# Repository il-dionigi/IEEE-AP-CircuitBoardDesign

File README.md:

# Schematic and Board Design
*05 February 2018 (Schematic)*

*16 February 2018 (PCB)*

This repo contains both the schematic and board files for our PCB made using EAGLE.  

Creating the schematic and board involved the culmination of all previous labs, as each of the components and wiring setups were tested or designed by our group.

The specs for both parts can be found in [schematic-spec.pdf](https://github.com/il-dionigi/Circuit-Board-Design/blob/master/schematic-spec.pdf) and [board-spec.pdf](https://github.com/il-dionigi/Circuit-Board-Design/blob/master/schematic-spec.pdf) respectively. Screenshots of the schematic may be found [here](https://github.com/il-dionigi/Circuit-Board-Design/blob/master/SchematicPictures) while screenshots of the pcb may be found [here](https://github.com/il-dionigi/Circuit-Board-Design/blob/master/BoardPictures).

**Collaborators:**  
[Brian Raymond](https://github.com/il-dionigi) | [Kevin Ke-En Sun](https://github.com/inherentlyMalicious) | [Koji Kusumi](https://github.com/kojiboji) | [Rob Griffith](https://github.com/rwgriffithv)

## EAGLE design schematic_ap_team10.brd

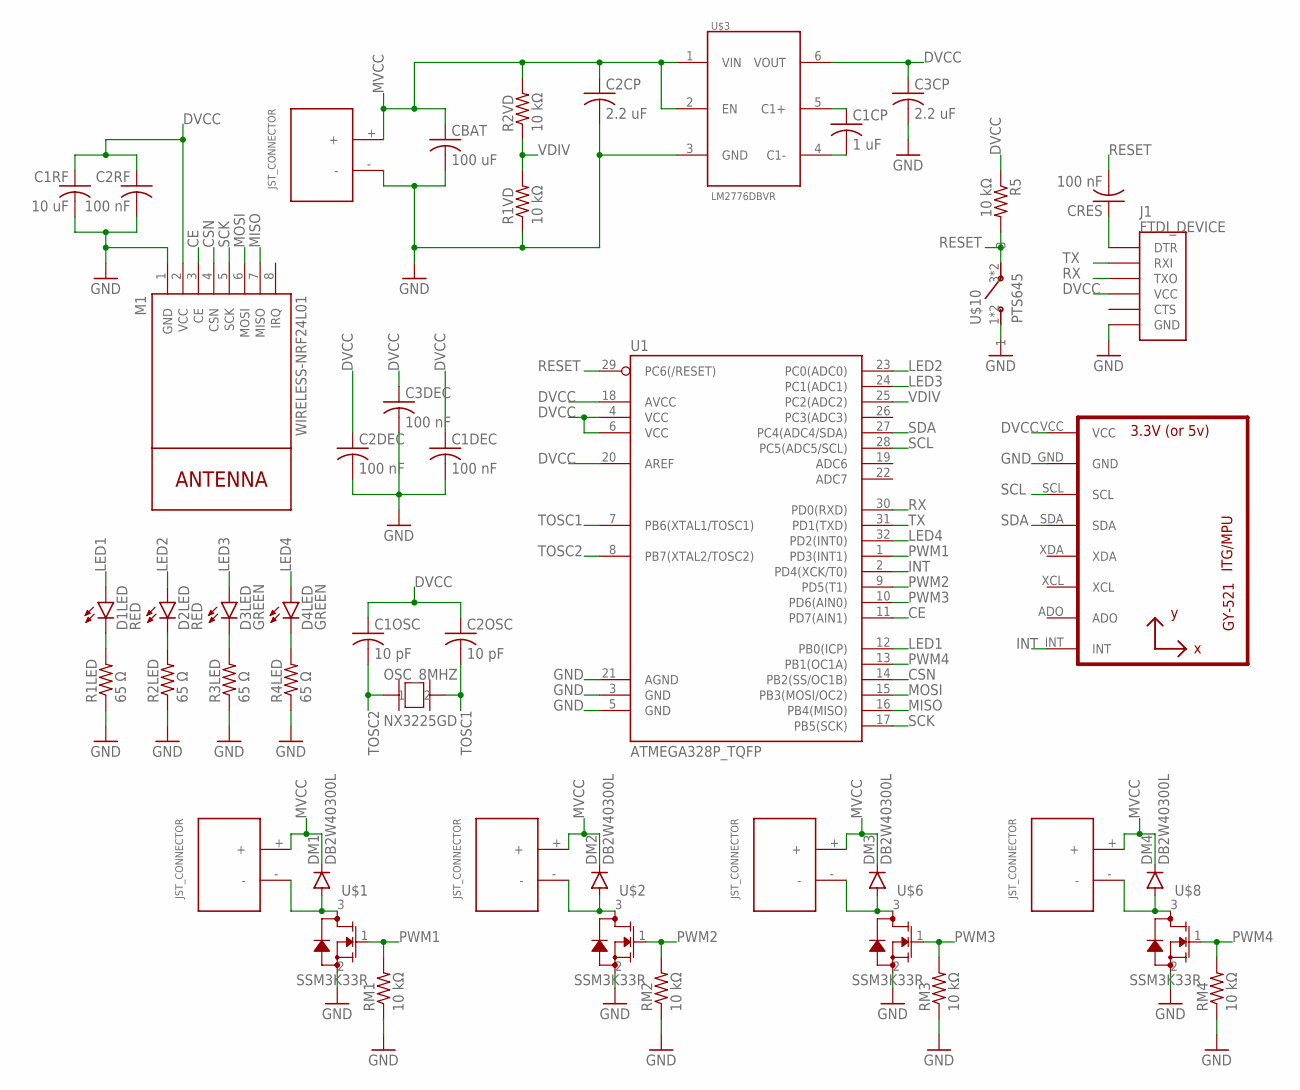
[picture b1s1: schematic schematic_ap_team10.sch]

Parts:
C1CP: 1 uF; C0603
C1DEC, C2DEC, C2RF, C3DEC: 100 nF; C0603
C1OSC, C2OSC: 10 pF; C0603
C1RF: 10 uF; C0603
C2CP, C3CP: 2.2 uF; C0603
CBAT: 100 uF; C0805
CRES: 100 nF; C0603
D1LED, D2LED: RED; LED-0603
D3LED, D4LED: GREEN; LED-0603
DM1, DM2, DM3, DM4: DB2W40300L; MINI2-F3-B
J1: FTDI_DEVICE; FTDI_DEVICE_SIDE
M1: WIRELESS-NRF24L01
OSC_8MHZ: NX3225GD; 2-SMD
R1LED, R2LED, R3LED, R4LED: 65 Ω; R0603
R1VD, R2VD, R5: 10 kΩ; R0603
RM1, RM2, RM3, RM4: 10 kΩ; R0603
U1: ATMEGA328P_TQFP; TQFP32-08
U2: GY-521MPU6050; GY-521
U$1, U$2, U$6, U$8: SSM3K33R; SOT-23F
U$3: LM2776DBVR; SOT23-5
U$4, U$5, U$7, U$9, U$11: JST_CONNECTOR_FEMALE
U$10: PTS645; SOT-35

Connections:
CE: M1.3 (CE), U1.11 (PD7(AIN1))
CSN: M1.4 (CSN), U1.14 (PB2(SS/OC1B))
DVCC: C1DEC.1, C1OSC.1, C1RF.1, C2DEC.1, C2OSC.1, C2RF.1, C3CP.1, C3DEC.1, J1.P$4 (VCC), M1.2 (VCC), R5.1, U1.4 (VCC), U1.6 (VCC), U1.18 (AVCC), U1.20 (AREF), U2.VCC, U$3.6 (VOUT)
GND: C1DEC.2, C1RF.2, C2CP.2, C2DEC.2, C2RF.2, C3CP.2, C3DEC.2, CBAT.2, J1.P$6 (GND), M1.1 (GND), R1LED.1, R1VD.1, R2LED.1, R3LED.1, R4LED.1, RM1.1, RM2.1, RM3.1, RM4.1, U1.3 (GND), U1.5 (GND), U1.21 (AGND), U2.GND, U$1.2, U$2.2, U$3.3 (GND), U$6.2, U$8.2, U$10.1, U$10.2 (1), U$11.-
INT: U1.2 (PD4(XCK/T0)), U2.INT
LED1: D1LED.A, U1.12 (PB0(ICP))
LED2: D2LED.A, U1.23 (PC0(ADC0))
LED3: D3LED.A, U1.24 (PC1(ADC1))
LED4: D4LED.A, U1.32 (PD2(INT0))
MISO: M1.7 (MISO), U1.16 (PB4(MISO))
MOSI: M1.6 (MOSI), U1.15 (PB3(MOSI/OC2))
MVCC: C2CP.1, CBAT.1, DM1.NEG (GPIN), DM2.NEG (GPIN), DM3.NEG (GPIN), DM4.NEG (GPIN), R2VD.2, U$3.1 (VIN), U$3.2 (EN), U$4.+, U$5.+, U$7.+, U$9.+, U$11.+
unnamed: DM1.POS (PPIN), U$1.3, U$4.-
unnamed: DM2.POS (PPIN), U$2.3, U$5.-
unnamed: CRES.1, J1.P$1 (DTR)
unnamed: DM3.POS (PPIN), U$6.3, U$7.-
unnamed: DM4.POS (PPIN), U$8.3, U$9.-
unnamed: C1CP.1, U$3.5 (C1+)
unnamed: C1CP.2, U$3.4 (C1-)
unnamed: D4LED.C, R4LED.2
unnamed: D2LED.C, R2LED.2
unnamed: D3LED.C, R3LED.2
unnamed: D1LED.C, R1LED.2
PWM1: RM1.2, U1.1 (PD3(INT1)), U$1.1
PWM2: RM2.2, U1.9 (PD5(T1)), U$2.1
PWM3: RM3.2, U1.10 (PD6(AIN0)), U$6.1
PWM4: RM4.2, U1.13 (PB1(OC1A)), U$8.1
RESET: CRES.2, R5.2, U1.29 (PC6(/RESET)), U$10.3, U$10.4 (3)
RX: J1.P$3 (TXO), U1.30 (PD0(RXD))
SCK: M1.5 (SCK), U1.17 (PB5(SCK))
SCL: U1.28 (PC5(ADC5/SCL)), U2.SCL
SDA: U1.27 (PC4(ADC4/SDA)), U2.SDA
TOSC1: C2OSC.2, OSC_8MHZ.2, U1.7 (PB6(XTAL1/TOSC1))
TOSC2: C1OSC.2, OSC_8MHZ.1, U1.8 (PB7(XTAL2/TOSC2))
TX: J1.P$2 (RXI), U1.31 (PD1(TXD))
VDIV: R1VD.2, R2VD.1, U1.25 (PC2(ADC2))

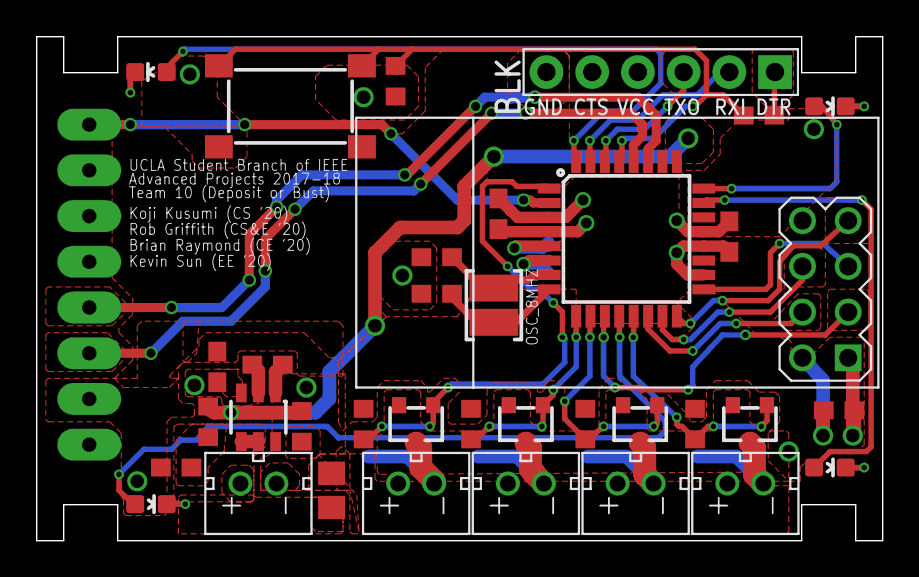
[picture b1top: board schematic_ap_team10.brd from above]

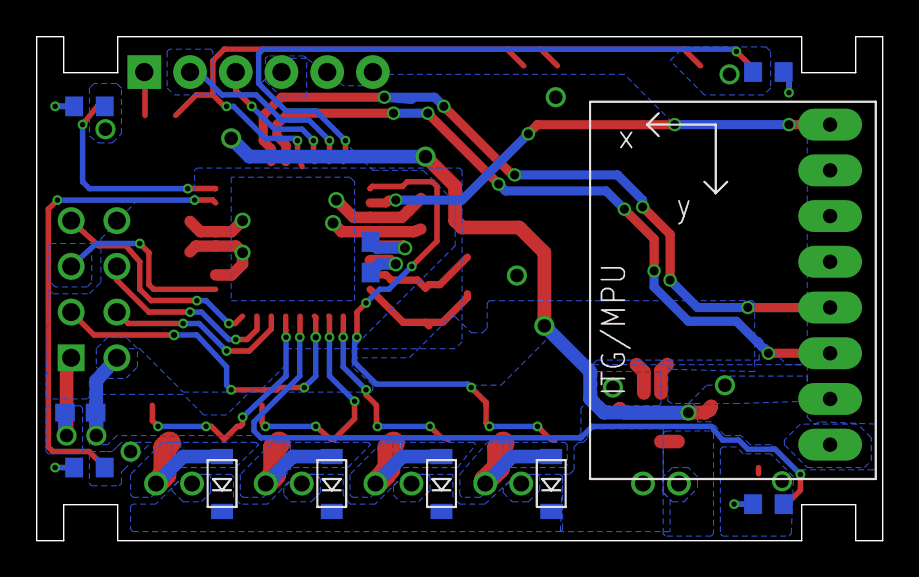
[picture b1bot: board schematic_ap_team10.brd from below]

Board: 2 copper layers, 47.0 x 28.0 mm, 47 parts (11 on the bottom side), 36 nets.

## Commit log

2018-01-20 Initial commit
    init
2018-01-20 init base
    Added requires libraries for Eagle and the base file with some components
2018-01-21 Library organization + charge pump
    Organized the needed library files and created the charge pump using the datasheet with Rob
2018-01-21 Deleted copies
    Deleted copies from the original location of the library files
2018-01-21 Added parts
    Added parts to schematic
2018-01-21 MOSFET init lbr file
    Initial MOSFET file, not yet complete. Need to change pin numbers to be 1-1
2018-01-21 NMOS Library
    Created the NMOS library w/Rob and added it to the schematic
2018-01-22 Oscillator symbol/footprint
    Created library file for our 16MHz oscillator and added it to the schematic
2018-01-22 Crystal Circuit
    Wired the crystal on the board layout and adjusted the lbr file
2018-01-22 Decoupler and charge pump
    Added a decoupler to the AREF and adjusted the pad size on the charge pump
2018-01-23 Basic Schematic
    Schematic with Motor Low-side Driver and Crystal
2018-01-23 IMU Wiring
    Wired IMU on the layout
2018-01-23 Wired Radio
    Wired the radio to the correct pins and moved around the motor.
2018-01-23 Wired radio
    Moved around motors to wire radio and connected the radio
2018-01-23 LED Schematic + Battery
    Wired the LEDs on the symbol schematic and connected the battery. Still no chargepump
2018-01-23 Changed ChargePump
    Changed chargepump to a different model with different pin names but the same pads.
2018-01-23 Wired chargepump
    Wired the charge pump to the symbol schematic and added the capacitors and battery (jst junction for now).
2018-01-28 New schematic file
    New file for schematic
2018-01-29 New Oscillator
    Added the 8MHZ Oscillator
2018-01-29 More wiring
2018-01-29 Schematic Wiring
    Wiring of parts
2018-01-29 Reset Pin Wiring
    Wired reset pin
2018-01-29 Pre-Schematic Review Finalized Version
2018-01-29 Actual Pre-Schematic Review Finalized Version
    Foooo real
2018-01-29 Updated Symbols
    Made the symbols for NMOS and Oscillator look better
2018-01-29 NMOS Symbol Minor Change
    Moved the symbol so that the center marker isn't visible and is covered.
2018-01-31 Post-Design Changes
    Changes according to recommendations
2018-02-01 Deleted Bad Schematic
    Got rid of the old, bad schematic
2018-02-01 Random Nets
    Got rid of some stray nets
2018-02-02 FTDI Fix
    Fixed library file for FTDI and schematic
2018-02-07 Final schematic
    Final schematic plus the spec for that lab
2018-02-07 Board Init
    Initial dimensions and cutouts for the board
2018-02-08 Board Layout #1
    Board layout - ground style one
2018-02-08 Board Layout #2
    This layout seems better, but can the grounds and powers be connected?
2018-02-08 Pre-Ground Changes
    Seperating the grounds on the motor drivers
2018-02-09 Pre-Polygons
2018-02-09 First Draft
2018-02-09 File name cleanup
    Got rid of old files, and unneeded eagle files
2018-02-09 Schematic Photos
    Pictures of schematic components
2018-02-09 Cap change
    Moved the 0805 cap to the side
2018-02-13 Pre-4th Attempt
    Need to move the JSTs
2018-02-13 5th Draft
    Changed the layout to have JSTs on the side
2018-02-17 Actual 5th (final?) Draft
    Changed some parts as well (the oscillator) and moved stuff around.
2018-02-18 clean up
    upated readme and added screenshots of work
2018-02-18 Readme link fixing
    Fixed some of the links (for github) in the readme
2018-02-22 LED Resistor Update
    150Ohm -> 65Ohm
